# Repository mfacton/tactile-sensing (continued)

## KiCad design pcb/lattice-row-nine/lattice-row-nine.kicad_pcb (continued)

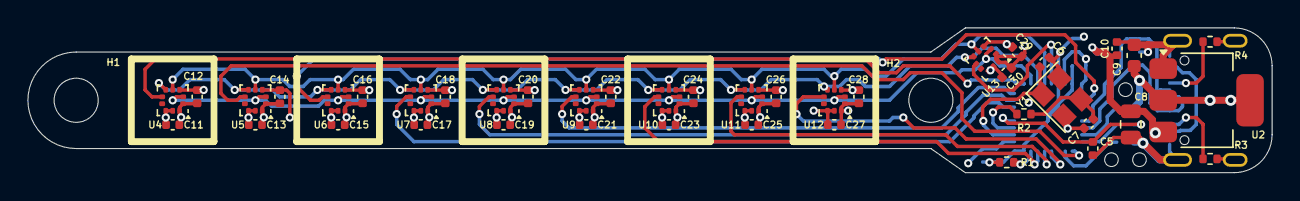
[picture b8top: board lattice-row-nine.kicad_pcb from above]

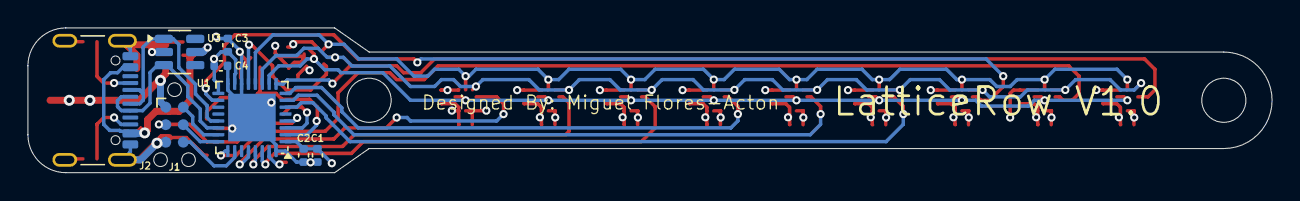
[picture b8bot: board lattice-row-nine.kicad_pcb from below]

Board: 4 copper layers, 90.2 x 10.5 mm, 52 parts (8 on the bottom side), 28 nets.

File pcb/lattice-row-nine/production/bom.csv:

Designator,Footprint,Quantity,Value,LCSC Part #
C1,0402,1,10u,C15525
C10,0402,1,1u,C52923
"C11, C13, C15, C17, C19, C21, C23, C25, C27, C29",0402,10,4u7,C23733
"C12, C14, C16, C18, C2, C20, C22, C24, C26, C28, C3, C30, C4, C5",0402,14,100n,C1525
"C6, C7",0402,2,10p,C32949
C8,0805,1,22u,C45783
C9,0603,1,22u,C59461
J2,USB_C_Receptacle_GCT_USB4105-xx-A_16P_TopMnt_Horizontal,1,USB_C_Receptacle_USB2.0_16P,C2765186
R1,0402,1,10k,C25744
R2,0402,1,510,C25123
"R3, R4",0402,2,5k1,C25905
U1,QFN-32-1EP_5x5mm_P0.5mm_EP3.45x3.45mm,1,STM32G431KBUx,C1341901
"U10, U11, U12, U13, U4, U5, U6, U7, U8, U9",ST_HLGA-10_2x2mm_P0.5mm_LayoutBorder3x2y,10,LPS22HH,C2827824
U2,SOT-223-3_TabPin2,1,AMS1117-3.3,C6186
U3,SOT-23-6,1,SRV05-4,C7420376
Y1,Crystal_SMD_3225-4Pin_3.2x2.5mm,1,16MHz,C13738

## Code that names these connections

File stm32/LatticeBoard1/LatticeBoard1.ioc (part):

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Mcu.Name=STM32F407V(E-G)Tx
Mcu.Package=LQFP100
Mcu.UserName=STM32F407VETx
PA10.GPIOParameters=GPIO_Speed,PinState,GPIO_Label
PA10.GPIO_Label=CSA14
PA10.GPIO_Speed=GPIO_SPEED_FREQ_HIGH
PA10.PinState=GPIO_PIN_SET
PA10.Signal=GPIO_Output
PA11.Mode=Device_Only
PA11.Signal=USB_OTG_FS_DM
PA12.Mode=Device_Only
PA12.Signal=USB_OTG_FS_DP
PA13.Mode=Trace_Asynchronous_SW
PA13.Signal=SYS_JTMS-SWDIO
PA14.Mode=Trace_Asynchronous_SW
PA14.Signal=SYS_JTCK-SWCLK
PA5.Mode=Full_Duplex_Master
PA5.Signal=SPI1_SCK
PA6.Mode=Full_Duplex_Master
PA6.Signal=SPI1_MISO
PA7.Mode=Full_Duplex_Master
PA7.Signal=SPI1_MOSI
PA8.GPIOParameters=GPIO_Speed,PinState,GPIO_Label
PA8.GPIO_Label=CSA15
PA8.GPIO_Speed=GPIO_SPEED_FREQ_HIGH
PA8.PinState=GPIO_PIN_SET
PA8.Signal=GPIO_Output
PA9.Mode=Activate_VBUS
PA9.Signal=USB_OTG_FS_VBUS
PB0.GPIOParameters=GPIO_Speed,PinState,GPIO_Label
PB0.GPIO_Label=CSC13
PB0.GPIO_Speed=GPIO_SPEED_FREQ_HIGH
PB0.PinState=GPIO_PIN_SET
PB0.Signal=GPIO_Output
PB10.Mode=Full_Duplex_Master
PB10.Signal=SPI2_SCK
PB12.GPIOParameters=GPIO_Speed,PinState,GPIO_Label
PB12.GPIO_Label=CSB10
PB12.GPIO_Speed=GPIO_SPEED_FREQ_HIGH
PB12.PinState=GPIO_PIN_SET
PB12.Signal=GPIO_Output
PB13.GPIOParameters=GPIO_Speed,PinState,GPIO_Label
PB13.GPIO_Label=CSB9
PB13.GPIO_Speed=GPIO_SPEED_FREQ_HIGH
PB13.PinState=GPIO_PIN_SET
PB13.Signal=GPIO_Output
PB14.GPIOParameters=GPIO_Speed,PinState,GPIO_Label
PB14.GPIO_Label=CSC8
PB14.GPIO_Speed=GPIO_SPEED_FREQ_HIGH
PB14.PinState=GPIO_PIN_SET
PB14.Signal=GPIO_Output
PB15.GPIOParameters=GPIO_Speed,PinState,GPIO_Label
PB15.GPIO_Label=CSB8
PB15.GPIO_Speed=GPIO_SPEED_FREQ_HIGH
PB15.PinState=GPIO_PIN_SET
PB15.Signal=GPIO_Output
PB2.GPIOParameters=GPIO_Speed,PinState,GPIO_Label
PB2.GPIO_Label=CSC12
PB2.GPIO_Speed=GPIO_SPEED_FREQ_HIGH
PB2.PinState=GPIO_PIN_SET
PB2.Signal=GPIO_Output
PB3.Mode=Trace_Asynchronous_SW
PB3.Signal=SYS_JTDO-SWO
PB4.GPIOParameters=GPIO_Speed,PinState,GPIO_Label
PB4.GPIO_Label=CSC9
PB4.GPIO_Speed=GPIO_SPEED_FREQ_HIGH
PB4.PinState=GPIO_PIN_SET
PB4.Signal=GPIO_Output
PB5.GPIOParameters=GPIO_Speed,PinState,GPIO_Label
PB5.GPIO_Label=CSC10
PB5.GPIO_Speed=GPIO_SPEED_FREQ_HIGH
PB5.PinState=GPIO_PIN_SET
PB5.Signal=GPIO_Output
PB6.Mode=I2C
PB6.Signal=I2C1_SCL
PB7.Mode=I2C
PB7.Signal=I2C1_SDA
PB8.GPIOParameters=GPIO_Speed,PinState,GPIO_Label
PB8.GPIO_Label=CSA5
PB8.GPIO_Speed=GPIO_SPEED_FREQ_HIGH
PB8.PinState=GPIO_PIN_SET
PB8.Signal=GPIO_Output
PB9.GPIOParameters=GPIO_Speed,PinState,GPIO_Label
PB9.GPIO_Label=CSA4
PB9.GPIO_Speed=GPIO_SPEED_FREQ_HIGH
PB9.PinState=GPIO_PIN_SET
PB9.Signal=GPIO_Output
PC10.Mode=Full_Duplex_Master
PC10.Signal=SPI3_SCK
PC11.Mode=Full_Duplex_Master
PC11.Signal=SPI3_MISO
PC12.Mode=Full_Duplex_Master
PC12.Signal=SPI3_MOSI
PC2.Mode=Full_Duplex_Master
PC2.Signal=SPI2_MISO
PC3.Mode=Full_Duplex_Master
PC3.Signal=SPI2_MOSI
PC4.GPIOParameters=GPIO_Speed,PinState,GPIO_Label
PC4.GPIO_Label=CSC15
PC4.GPIO_Speed=GPIO_SPEED_FREQ_HIGH
PC4.PinState=GPIO_PIN_SET
PC4.Signal=GPIO_Output
PC5.GPIOParameters=GPIO_Speed,PinState,GPIO_Label
PC5.GPIO_Label=CSC14
PC5.GPIO_Speed=GPIO_SPEED_FREQ_HIGH
PC5.PinState=GPIO_PIN_SET
PC5.Signal=GPIO_Output
PC7.GPIOParameters=GPIO_Speed,PinState,GPIO_Label
PC7.GPIO_Label=CSB3
PC7.GPIO_Speed=GPIO_SPEED_FREQ_HIGH
PC7.PinState=GPIO_PIN_SET
PC7.Signal=GPIO_Output
PC8.GPIOParameters=GPIO_Speed,PinState,GPIO_Label
PC8.GPIO_Label=CSB2
PC8.GPIO_Speed=GPIO_SPEED_FREQ_HIGH
PC8.PinState=GPIO_PIN_SET
PC8.Signal=GPIO_Output
PC9.GPIOParameters=GPIO_Speed,PinState,GPIO_Label
PC9.GPIO_Label=CSB1
PC9.GPIO_Speed=GPIO_SPEED_FREQ_HIGH
PC9.PinState=GPIO_PIN_SET
PC9.Signal=GPIO_Output
PD0.GPIOParameters=GPIO_Speed,PinState,GPIO_Label
PD0.GPIO_Label=CSA8
PD0.GPIO_Speed=GPIO_SPEED_FREQ_HIGH
PD0.PinState=GPIO_PIN_SET
PD0.Signal=GPIO_Output
PD1.GPIOParameters=GPIO_Speed,PinState,GPIO_Label
PD1.GPIO_Label=CSA9
PD1.GPIO_Speed=GPIO_SPEED_FREQ_HIGH
PD1.PinState=GPIO_PIN_SET
PD1.Signal=GPIO_Output
PD10.GPIOParameters=GPIO_Speed,PinState,GPIO_Label
PD10.GPIO_Label=CSC6
PD10.GPIO_Speed=GPIO_SPEED_FREQ_HIGH
PD10.PinState=GPIO_PIN_SET
PD10.Signal=GPIO_Output
PD11.GPIOParameters=GPIO_Speed,PinState,GPIO_Label
PD11.GPIO_Label=CSB6
PD11.GPIO_Speed=GPIO_SPEED_FREQ_HIGH
PD11.PinState=GPIO_PIN_SET
PD11.Signal=GPIO_Output
PD12.GPIOParameters=GPIO_Speed,PinState,GPIO_Label
PD12.GPIO_Label=CSC5
PD12.GPIO_Speed=GPIO_SPEED_FREQ_HIGH
PD12.PinState=GPIO_PIN_SET
PD12.Signal=GPIO_Output
PD13.GPIOParameters=GPIO_Speed,PinState,GPIO_Label
PD13.GPIO_Label=CSB5
PD13.GPIO_Speed=GPIO_SPEED_FREQ_HIGH
PD13.PinState=GPIO_PIN_SET
PD13.Signal=GPIO_Output
PD14.GPIOParameters=GPIO_Speed,PinState,GPIO_Label
PD14.GPIO_Label=CSC4
PD14.GPIO_Speed=GPIO_SPEED_FREQ_HIGH
PD14.PinState=GPIO_PIN_SET
PD14.Signal=GPIO_Output
PD15.GPIOParameters=GPIO_Speed,PinState,GPIO_Label
PD15.GPIO_Label=CSB4
PD15.GPIO_Speed=GPIO_SPEED_FREQ_HIGH
PD15.PinState=GPIO_PIN_SET
PD15.Signal=GPIO_Output
PD2.GPIOParameters=GPIO_Speed,PinState,GPIO_Label
PD2.GPIO_Label=CSA10
PD2.GPIO_Speed=GPIO_SPEED_FREQ_HIGH
PD2.PinState=GPIO_PIN_SET
PD2.Signal=GPIO_Output
PD3.GPIOParameters=GPIO_Speed,PinState,GPIO_Label
PD3.GPIO_Label=CSA7
PD3.GPIO_Speed=GPIO_SPEED_FREQ_HIGH
PD3.PinState=GPIO_PIN_SET
PD3.Signal=GPIO_Output
PD4.GPIOParameters=GPIO_Speed,PinState,GPIO_Label
PD4.GPIO_Label=CSA6
PD4.GPIO_Speed=GPIO_SPEED_FREQ_HIGH
PD4.PinState=GPIO_PIN_SET
PD4.Signal=GPIO_Output
PD5.GPIOParameters=GPIO_Speed,PinState,GPIO_Label
PD5.GPIO_Label=CSA11
PD5.GPIO_Speed=GPIO_SPEED_FREQ_HIGH
PD5.PinState=GPIO_PIN_SET
PD5.Signal=GPIO_Output
PD6.GPIOParameters=GPIO_Speed,PinState,GPIO_Label
PD6.GPIO_Label=CSA12
PD6.GPIO_Speed=GPIO_SPEED_FREQ_HIGH
PD6.PinState=GPIO_PIN_SET
PD6.Signal=GPIO_Output
PD7.GPIOParameters=GPIO_Speed,PinState,GPIO_Label
PD7.GPIO_Label=CSA13
PD7.GPIO_Speed=GPIO_SPEED_FREQ_HIGH
PD7.PinState=GPIO_PIN_SET
PD7.Signal=GPIO_Output
PD8.GPIOParameters=GPIO_Speed,PinState,GPIO_Label
PD8.GPIO_Label=CSC7
PD8.GPIO_Speed=GPIO_SPEED_FREQ_HIGH
PD8.PinState=GPIO_PIN_SET
PD8.Signal=GPIO_Output
PD9.GPIOParameters=GPIO_Speed,PinState,GPIO_Label
PD9.GPIO_Label=CSB7
PD9.GPIO_Speed=GPIO_SPEED_FREQ_HIGH
PD9.PinState=GPIO_PIN_SET
PD9.Signal=GPIO_Output
PE0.GPIOParameters=GPIO_Speed,PinState,GPIO_Label
PE0.GPIO_Label=CSA3
PE0.GPIO_Speed=GPIO_SPEED_FREQ_HIGH
PE0.PinState=GPIO_PIN_SET
PE0.Signal=GPIO_Output
PE1.GPIOParameters=GPIO_Speed,PinState,GPIO_Label
PE1.GPIO_Label=CSA2
PE1.GPIO_Speed=GPIO_SPEED_FREQ_HIGH
PE1.PinState=GPIO_PIN_SET
PE1.Signal=GPIO_Output
PE10.GPIOParameters=GPIO_Speed,PinState,GPIO_Label
PE10.GPIO_Label=CSC1
PE10.GPIO_Speed=GPIO_SPEED_FREQ_HIGH
PE10.PinState=GPIO_PIN_SET
PE10.Signal=GPIO_Output
PE11.GPIOParameters=GPIO_Speed,PinState,GPIO_Label
PE11.GPIO_Label=CSB15
PE11.GPIO_Speed=GPIO_SPEED_FREQ_HIGH
PE11.PinState=GPIO_PIN_SET
PE11.Signal=GPIO_Output
PE12.GPIOParameters=GPIO_Speed,PinState,GPIO_Label
PE12.GPIO_Label=CSB14
PE12.GPIO_Speed=GPIO_SPEED_FREQ_HIGH
PE12.PinState=GPIO_PIN_SET
PE12.Signal=GPIO_Output
PE13.GPIOParameters=GPIO_Speed,PinState,GPIO_Label
PE13.GPIO_Label=CSB13
PE13.GPIO_Speed=GPIO_SPEED_FREQ_HIGH
PE13.PinState=GPIO_PIN_SET
PE13.Signal=GPIO_Output
PE14.GPIOParameters=GPIO_Speed,PinState,GPIO_Label
PE14.GPIO_Label=CSB12
PE14.GPIO_Speed=GPIO_SPEED_FREQ_HIGH
PE14.PinState=GPIO_PIN_SET
PE14.Signal=GPIO_Output
PE15.GPIOParameters=GPIO_Speed,PinState,GPIO_Label
PE15.GPIO_Label=CSB11
PE15.GPIO_Speed=GPIO_SPEED_FREQ_HIGH
PE15.PinState=GPIO_PIN_SET
PE15.Signal=GPIO_Output
PE2.GPIOParameters=GPIO_Speed,PinState,GPIO_Label
PE2.GPIO_Label=CSA1
PE2.GPIO_Speed=GPIO_SPEED_FREQ_HIGH
PE2.PinState=GPIO_PIN_SET
PE2.Signal=GPIO_Output
PE3.GPIOParameters=GPIO_Speed,PinState,GPIO_Label
PE3.GPIO_Label=CSC11
PE3.GPIO_Speed=GPIO_SPEED_FREQ_HIGH
PE3.PinState=GPIO_PIN_SET
PE3.Signal=GPIO_Output
PE8.GPIOParameters=GPIO_Speed,PinState,GPIO_Label
PE8.GPIO_Label=CSC3
PE8.GPIO_Speed=GPIO_SPEED_FREQ_HIGH
PE8.PinState=GPIO_PIN_SET
PE8.Signal=GPIO_Output
PE9.GPIOParameters=GPIO_Speed,PinState,GPIO_Label
PE9.GPIO_Label=CSC2
PE9.GPIO_Speed=GPIO_SPEED_FREQ_HIGH
PE9.PinState=GPIO_PIN_SET
PE9.Signal=GPIO_Output
PH0-OSC_IN.Mode=HSE-External-Oscillator
PH0-OSC_IN.Signal=RCC_OSC_IN
PH1-OSC_OUT.Mode=HSE-External-Oscillator
PH1-OSC_OUT.Signal=RCC_OSC_OUT
RCC.HSE_VALUE=16000000
RCC.SYSCLKFreq_VALUE=168000000
RCC.SYSCLKSource=RCC_SYSCLKSOURCE_PLLCLK
board=custom

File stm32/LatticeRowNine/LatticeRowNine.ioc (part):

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Mcu.Name=STM32G431K(6-8-B)Ux
Mcu.Package=UFQFPN32
Mcu.UserName=STM32G431KBUx
PA1.GPIOParameters=GPIO_Speed,PinState,GPIO_Label
PA1.GPIO_Label=CS4
PA1.GPIO_Speed=GPIO_SPEED_FREQ_VERY_HIGH
PA1.PinState=GPIO_PIN_SET
PA1.Signal=GPIO_Output
PA11.Mode=Device
PA11.Signal=USB_DM
PA12.Mode=Device
PA12.Signal=USB_DP
PA13.Mode=Trace_Asynchronous_SW
PA13.Signal=SYS_JTMS-SWDIO
PA14.Mode=Trace_Asynchronous_SW
PA14.Signal=SYS_JTCK-SWCLK
PA15.GPIOParameters=GPIO_Speed,PinState,GPIO_Label
PA15.GPIO_Label=CS2
PA15.GPIO_Speed=GPIO_SPEED_FREQ_VERY_HIGH
PA15.PinState=GPIO_PIN_SET
PA15.Signal=GPIO_Output
PA2.GPIOParameters=GPIO_Speed,PinState,GPIO_Label
PA2.GPIO_Label=CS5
PA2.GPIO_Speed=GPIO_SPEED_FREQ_VERY_HIGH
PA2.PinState=GPIO_PIN_SET
PA2.Signal=GPIO_Output
PA3.GPIOParameters=GPIO_Speed,PinState,GPIO_Label
PA3.GPIO_Label=CS6
PA3.GPIO_Speed=GPIO_SPEED_FREQ_VERY_HIGH
PA3.PinState=GPIO_PIN_SET
PA3.Signal=GPIO_Output
PA4.GPIOParameters=GPIO_Speed,PinState,GPIO_Label
PA4.GPIO_Label=CS1
PA4.GPIO_Speed=GPIO_SPEED_FREQ_VERY_HIGH
PA4.PinState=GPIO_PIN_SET
PA4.Signal=GPIO_Output
PA5.GPIOParameters=GPIO_Speed
PA5.GPIO_Speed=GPIO_SPEED_FREQ_VERY_HIGH
PA5.Mode=Full_Duplex_Master
PA5.Signal=SPI1_SCK
PA6.GPIOParameters=GPIO_Speed
PA6.GPIO_Speed=GPIO_SPEED_FREQ_VERY_HIGH
PA6.Mode=Full_Duplex_Master
PA6.Signal=SPI1_MISO
PA7.GPIOParameters=GPIO_Speed
PA7.GPIO_Speed=GPIO_SPEED_FREQ_VERY_HIGH
PA7.Mode=Full_Duplex_Master
PA7.Signal=SPI1_MOSI
PA8.GPIOParameters=GPIO_Speed,PinState,GPIO_Label
PA8.GPIO_Label=CS3
PA8.GPIO_Speed=GPIO_SPEED_FREQ_VERY_HIGH
PA8.PinState=GPIO_PIN_SET
PA8.Signal=GPIO_Output
PB0.GPIOParameters=GPIO_Speed,PinState,GPIO_Label
PB0.GPIO_Label=CS10
PB0.GPIO_Speed=GPIO_SPEED_FREQ_VERY_HIGH
PB0.PinState=GPIO_PIN_SET
PB0.Signal=GPIO_Output
PB3.Mode=Trace_Asynchronous_SW
PB3.Signal=SYS_JTDO-SWO
PB5.GPIOParameters=GPIO_Speed,PinState,GPIO_Label
PB5.GPIO_Label=CS9
PB5.GPIO_Speed=GPIO_SPEED_FREQ_VERY_HIGH
PB5.PinState=GPIO_PIN_SET
PB5.Signal=GPIO_Output
PB6.GPIOParameters=GPIO_Speed,PinState,GPIO_Label
PB6.GPIO_Label=CS8
PB6.GPIO_Speed=GPIO_SPEED_FREQ_VERY_HIGH
PB6.PinState=GPIO_PIN_SET
PB6.Signal=GPIO_Output
PB7.GPIOParameters=GPIO_Speed,PinState,GPIO_Label
PB7.GPIO_Label=CS7
PB7.GPIO_Speed=GPIO_SPEED_FREQ_VERY_HIGH
PB7.PinState=GPIO_PIN_SET
PB7.Signal=GPIO_Output
PF0-OSC_IN.Mode=HSE-External-Oscillator
PF0-OSC_IN.Signal=RCC_OSC_IN
PF1-OSC_OUT.Mode=HSE-External-Oscillator
PF1-OSC_OUT.Signal=RCC_OSC_OUT
RCC.HSE_VALUE=16000000
RCC.SYSCLKFreq_VALUE=144000000
RCC.SYSCLKSource=RCC_SYSCLKSOURCE_PLLCLK
board=custom

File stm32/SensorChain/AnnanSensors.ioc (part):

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Mcu.Name=STM32F411C(C-E)Ux
Mcu.Package=UFQFPN48
Mcu.UserName=STM32F411CEUx
PA0-WKUP.GPIOParameters=GPIO_Label,GPIO_Mode
PA0-WKUP.GPIO_Label=DR1
PA0-WKUP.GPIO_Mode=GPIO_MODE_INPUT
PA0-WKUP.Signal=GPIO_Input
PA1.GPIOParameters=GPIO_Label
PA1.GPIO_Label=DR2
PA1.Signal=GPIO_Input
PA11.Mode=Device_Only
PA11.Signal=USB_OTG_FS_DM
PA12.Mode=Device_Only
PA12.Signal=USB_OTG_FS_DP
PA13.Mode=Trace_Asynchronous_SW
PA13.Signal=SYS_JTMS-SWDIO
PA14.Mode=Trace_Asynchronous_SW
PA14.Signal=SYS_JTCK-SWCLK
PA2.GPIOParameters=GPIO_Label
PA2.GPIO_Label=DR3
PA2.Signal=GPIO_Input
PA3.GPIOParameters=GPIO_Label
PA3.GPIO_Label=DR6
PA3.Signal=GPIO_Input
PA4.GPIOParameters=GPIO_Label
PA4.GPIO_Label=DR5
PA4.Signal=GPIO_Input
PA5.Mode=Full_Duplex_Master
PA5.Signal=SPI1_SCK
PA6.Mode=Full_Duplex_Master
PA6.Signal=SPI1_MISO
PA7.Mode=Full_Duplex_Master
PA7.Signal=SPI1_MOSI
PA9.Mode=Activate_VBUS
PA9.Signal=USB_OTG_FS_VBUS
PB0.GPIOParameters=GPIO_Speed,PinState,GPIO_Label
PB0.GPIO_Label=CS1
PB0.GPIO_Speed=GPIO_SPEED_FREQ_HIGH
PB0.PinState=GPIO_PIN_SET
PB0.Signal=GPIO_Output
PB1.GPIOParameters=GPIO_Speed,PinState,GPIO_Label
PB1.GPIO_Label=CS2
PB1.GPIO_Speed=GPIO_SPEED_FREQ_HIGH
PB1.PinState=GPIO_PIN_SET
PB1.Signal=GPIO_Output
PB10.GPIOParameters=GPIO_Label
PB10.GPIO_Label=DR4
PB10.Signal=GPIO_Input
PB12.GPIOParameters=GPIO_Speed,PinState,GPIO_Label
PB12.GPIO_Label=CS4
PB12.GPIO_Speed=GPIO_SPEED_FREQ_HIGH
PB12.PinState=GPIO_PIN_SET
PB12.Signal=GPIO_Output
PB13.GPIOParameters=GPIO_Speed,PinState,GPIO_Label
PB13.GPIO_Label=CS5
PB13.GPIO_Speed=GPIO_SPEED_FREQ_HIGH
PB13.PinState=GPIO_PIN_SET
PB13.Signal=GPIO_Output
PB14.GPIOParameters=GPIO_Speed,PinState,GPIO_Label
PB14.GPIO_Label=CS6
PB14.GPIO_Speed=GPIO_SPEED_FREQ_HIGH
PB14.PinState=GPIO_PIN_SET
PB14.Signal=GPIO_Output
PB2.GPIOParameters=GPIO_Speed,PinState,GPIO_Label
PB2.GPIO_Label=CS3
PB2.GPIO_Speed=GPIO_SPEED_FREQ_HIGH
PB2.PinState=GPIO_PIN_SET
PB2.Signal=GPIO_Output
PB3.Mode=Trace_Asynchronous_SW
PB3.Signal=SYS_JTDO-SWO
PH0\ -\ OSC_IN.Mode=HSE-External-Oscillator
PH0\ -\ OSC_IN.Signal=RCC_OSC_IN
PH1\ -\ OSC_OUT.Mode=HSE-External-Oscillator
PH1\ -\ OSC_OUT.Signal=RCC_OSC_OUT
RCC.HSE_VALUE=16000000
RCC.SYSCLKFreq_VALUE=96000000
RCC.SYSCLKSource=RCC_SYSCLKSOURCE_PLLCLK
board=custom

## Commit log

2024-04-27 Make setup guide
2024-04-27 Prettyify README.md
2024-04-27 Fix small readme issues
2024-04-27 Add ur5 setup link
2024-04-27 Format kernel statement
2024-04-27 Combine apt update and upgrade
2024-04-27 Split setup environment section
2024-04-27 Cleanup setup environment section
2024-04-27 Add robot setup
2024-04-27 Add title
2024-04-27 Add create package instructions
2024-04-27 Fix capitalization
2024-04-27 Fix spelling
2024-04-27 Add build and source instructions
2024-04-27 Add example package
2024-04-27 Add gitignore
2024-04-27 Remove ignored ros files
2024-04-27 Add more ros2 basic commands
2024-04-28 Add test package
2024-05-02 Update driver launch
2024-05-03 Init stm32 workspace
2024-05-03 Init LatticeBoard stm project
2024-05-03 Add readme for stm32 folder
2024-05-03 Add readme for pcb folder
2024-05-03 Add arduino code and readme
2024-05-03 Change ros folder name
2024-05-03 Add pcb gitignore
2024-05-04 Update calibration file location
2024-05-04 Add install controllers and control
2024-05-04 Add moveit
2024-05-04 Use scaled joint controller
2024-05-04 Remove moveit dependency
2024-05-04 Fixed launch driver command
2024-05-04 Add activate scaled joint trajectory controller command
2024-05-04 Change to forward position controller
2024-05-04 Switch ip addresses
2024-05-04 Add docker command
2024-05-04 Fix docker stuff and ur_driver launch
2024-05-04 Add moveit launch
2024-05-04 Add ursim and test_position package
2024-05-05 Update arduino code
2024-05-05 Add moveit install
2024-05-05 Fix docker run code
2024-05-05 Add repo for ros2 ur driver
2024-05-05 sfsdjlnszn;gsf
2024-05-05 Fix universal robotics driver link
2024-05-05 Add ros1 folder
2024-05-05 Move ursim docker instructions to ursim folder
2024-05-06 Add plotter and serial manager
2024-05-06 Change arduino name
2024-05-07 Add pycache to gitignore
2024-05-07 Finish reader and arduino
2024-05-07 Change arduino code file
2024-05-07 Add read until function
2024-05-07 Change loop to memcpy for serial write
2024-05-08 Change plotter module name
2024-05-08 Add logger
2024-05-08 Rename sensor plotter
2024-05-08 Change plotter title to changable
2024-05-08 Change indexing for device nums in manager
2024-05-09 Add support for plotting multiple devices
2024-05-09 Finish plot logger
2024-05-10 Make micro carrier pcb
2024-05-10 Fix robot ip address
2024-05-10 Make arduino recieve newline to prevent crashes
2024-05-10 Add sampling features
2024-05-10 Move scripting files and data files
2024-05-10 Change scripting to script
2024-05-11 Reformat python files
2024-05-11 Fix script tools
2024-05-11 Add readme and .gitignore
2024-05-18 Remove backup folders
2024-05-18 Update proper pinout
2024-05-18 Ignore lck files
2024-05-18 Ignore production backups
2024-05-18 Unignore prodcution csvs
2024-05-18 Update version name silkmask
2024-05-31 Generate STEP file
2024-05-31 Update step model
2024-06-02 Remove time delay
2024-06-06 Add board fix notes
2024-06-06 Ignore stm32 debug
2024-06-06 Add old sensor chain code
2024-06-06 Add micro-carrier-flp
2024-06-06 Change filenames
2024-06-06 Save
2024-06-06 Remove test_position package
2024-06-06 Update gitignores
2024-06-06 Remove redundant ignore
2024-06-07 Fix step file name
2024-06-07 Add assembled headers
2024-06-07 Move notes to note dir
2024-06-07 Add lattice-board pcb
2024-06-08 Ignore schem autosave
2024-06-08 Add flex sensor grid idea pcb
2024-06-08 Update project
2024-06-08 Ignore .metadata folder
2024-06-08 Remove broken project
2024-06-08 Update and setup lattice board project
2024-06-08 Restore ioc
2024-06-08 Create lattice scripts
2024-06-08 Change scaling
2024-06-18 Finish schematic and routing and production
2024-06-18 Final production
2024-06-18 Setup ioc config
2024-06-18 Fix usb-device name
2024-06-18 Ignore USB_Device
2024-06-18 Remove USB_Device
2024-06-18 Add micro analog refrence silkmask
2024-06-19 Finish schematic
2024-06-19 Add part numbers
2024-06-23 Add write function
2024-06-23 Make background changable color
2024-06-23 Layout sizing
2024-06-23 Make plotter for latticeboard
2024-06-30 Create row nine plot script
2024-06-30 Program data output
2024-06-30 Remove old notes
2024-07-01 Add all 12 channels
2024-07-01 Rename plot_log
2024-07-04 Make probe board
2024-07-04 Add backups of octal geometry sensor layout
2024-07-09 Remove backups
2024-07-09 Add external control urcap
2024-07-09 Move urcap file
2024-07-09 Fix robot and network ips
2024-07-09 Update calibration file
2024-07-09 Add host id ip info
2024-07-15 Add auto scale and output selection
2024-07-16 Run signle channel comparison tests
2024-07-17 Add arduino node code
2024-07-17 Fix numpy array data
2024-07-17 Move arduino node
2024-07-17 Finish setting up probe
2024-07-17 Make probe ros node
2024-07-17 Fix baud rate
2024-07-17 Reinit projects
2024-07-18 Make moveit package
2024-07-18 Remove testing package
2024-07-18 Fix stray trace on pcb
2024-07-18 Get ursim calibration
2024-07-18 Fix index issue
2024-07-18 Make simple moveit package
2024-07-22 Add stm temperature integration
2024-07-22 Fix count configuration
2024-07-26 Save progress on using moveit2
2024-07-26 Save progress on sense-ring
2024-07-26 Finish load cell v1
2024-07-26 Setup interface pinout
2024-08-05 Final manufacture files
2024-08-05 Add feducials
2024-08-05 Debug probe board issues
2024-08-05 Setup rtde
2024-08-05 Add refrences
2024-08-07 Setup rtde on ursim
2024-08-07 Simple setup of rtde
2024-08-07 Add feducials and new manufacture data
2024-08-07 Add probe-eight firmware
2024-08-07 Revert lps read firmware
2024-08-07 Add probe-eight support
2024-08-07 Add urscript docs
2024-08-07 Change filter config
2024-08-07 Make smaller for less lag
2024-08-07 Move youtube example code
2024-08-08 Remove all old files
2024-08-08 Prepare to remove old rtde files
2024-08-08 Remove ur ros2 driver files
2024-08-08 Fix import for old rtde control
2024-08-08 Make a new readme for ros2
2024-08-08 Add vnc url to README
2024-08-08 Fix readme newlines
2024-08-09 Fix readme
2024-08-09 Add info to readme
2024-08-10 Remove depreciated readme info
2024-08-10 Remove symlink recommendation
2024-08-10 Test load cell sensors
2024-08-10 probe board stm readout
2024-08-10 Ignore program folder
2024-08-10 Add single probe reader node
2024-08-10 Add admittance control test
2024-08-12 Add disk and ring impedence nodes
2024-08-12 Rename center impedence
2024-08-12 Ignore ursim files
2024-08-12 Remove print angle
2024-08-12 Adjust speeds
2024-08-12 Change to sideways version
2024-08-12 Remove rtde folder
2024-08-13 Add origin shift maze generator
2024-08-13 Add animation flag
2024-08-15 Remove ros1 files
2024-08-15 Create load cell firmware
2024-08-15 Remove programs folder from gitignore
2024-08-15 Remove ur receive from soft control
2024-08-15 Fix package create info
2024-08-15 Add echo pose node
2024-08-15 Save mazegen
2024-08-15 Ignore vscode metadata
2024-08-15 Publish both tcp and joints
2024-08-15 Setup characterize plotting
2024-08-15 Setup interpret node
2024-08-15 Create soft map package
2024-08-15 Change pressure topic name
2024-08-15 Change pressure unit to pascals
2024-08-17 Ignore code counter
2024-08-27 Save probe board
2024-08-27 Create interpret node
2024-08-27 Change soft map node to python
2024-08-27 init map node
2024-08-27 Create graphics
2024-08-27 Move characterize node to sense package
2024-08-27 Finish interpet node
2024-09-10 Tune interpret parameter and depreciate characterize node
2024-09-10 Move old ros1 files and remove folder
2024-09-10 Create mapping
2024-09-10 Create ursim launch bash script
2024-09-10 Small changes to interpret node
2024-09-10 Add maze algorithm script
2024-09-11 Change interpret angles
2024-09-11 Randomly explore maze
2024-09-11 Create messages package
2024-09-12 Fix calibrate service requests
2024-09-12 Finish square maze solver
2024-09-12 Add final maze image
2024-09-14 Small changes
2024-09-27 Update Readme nodes and dynamixel info
2024-10-02 Update instructions
2024-10-02 Update plotter
2024-10-02 Add launch for sense package
2024-10-02 Add package info
2024-10-03 Set up demos
2024-10-03 Add demo instructions
2024-10-03 Add demo scripts
2024-10-03 Add usergroup info
2024-10-03 Fix network addresses
2024-10-03 Add demo info
2024-10-19 Add old boards
2024-10-19 Add old pcbs
2024-10-19 Rename files
2024-12-03 Initial layout
2024-12-05 Finish sense-ring
2024-12-13 Save 12 sensor
2025-03-12 Configure cmake
2025-03-12 Add drivers
2025-03-12 Add IDE Code
2025-03-13 Use library code
2025-03-14 Add CAN Speed
2025-03-22 Update Sensors
